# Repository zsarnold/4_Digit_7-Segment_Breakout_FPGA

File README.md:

# 4 Digit, 7-Segment Breakout FPGA

This breakout board was created to be used in my Ohio University Master's course. We were required to build this circuit on a breadboard but I wanted to help develop my PCB design skills. This is a 2 layer board and has 4 M3 mounting holes to add standoffs. This was designed using KiCAD and the PCB was produced by JLCPCB.

## Table of Contents
- [4 Digit, 7-Segment Breakout FPGA](#4-digit-7-segment-breakout-fpga)
  - [Table of Contents](#table-of-contents)
  - [BOM](#bom)
  - [Usage](#usage)
  - [License](#license)

## BOM
| Qty           | Reference     | Value         |
| ------------- | ------------- | ------------- |
| 1 | U1 | 4 Digit, 7-Segment Display |
| 1 | J1 | 1x13 2.54mm Header |
| 8 | R1-R8| 330&#937; (0603)
| 4 | R9-R12| 10k&#937; (0603)
| 4 | Q1-Q4| PN2222A (TO-92)
## Usage
## License

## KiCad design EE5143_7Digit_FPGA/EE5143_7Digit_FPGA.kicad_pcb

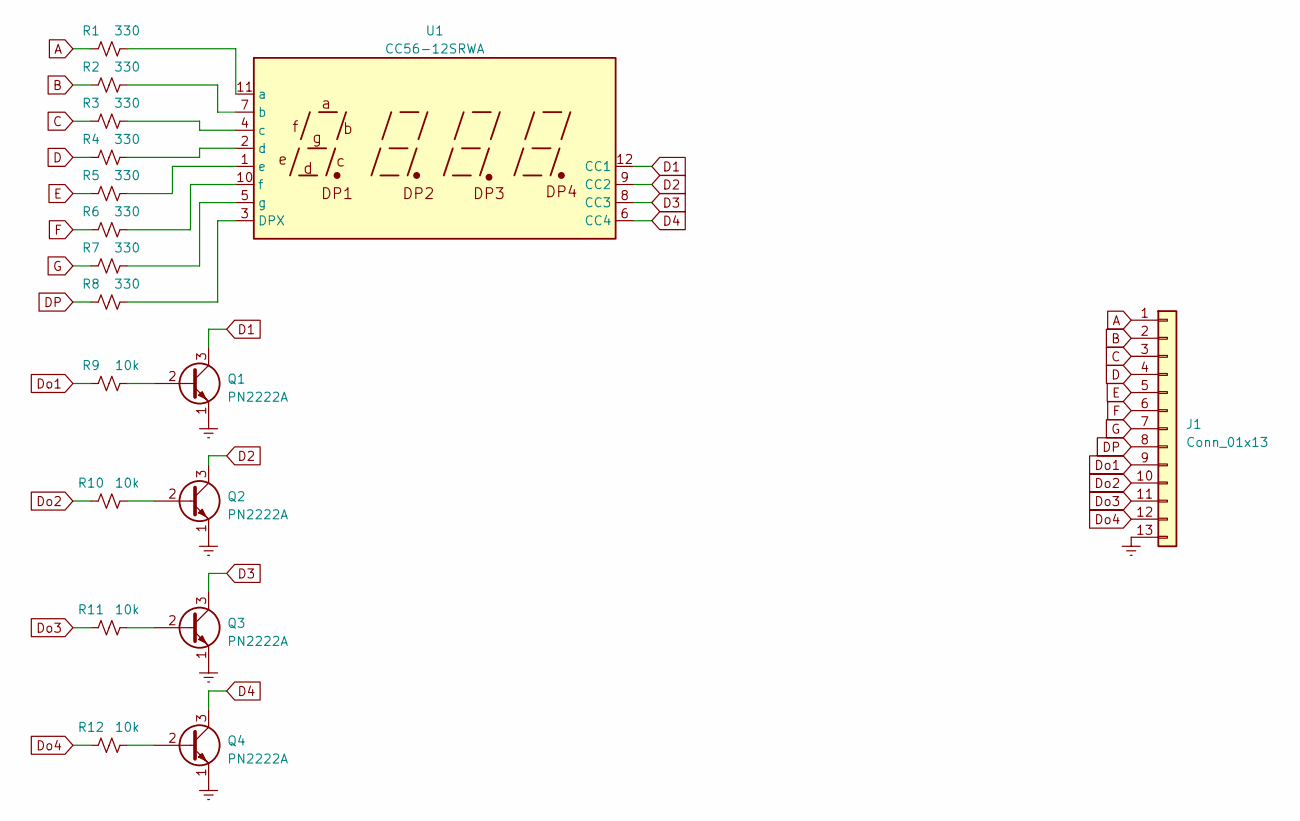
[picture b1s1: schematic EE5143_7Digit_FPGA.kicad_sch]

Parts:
J1: Conn_01x13; PinHeader_1x13_P2.54mm_Vertical
Q1, Q2, Q3, Q4: PN2222A; TO-92_Inline
R1, R2, R3, R4, R5, R6, R7, R8: 330; R_0603_1608Metric_Pad0.98x0.95mm_HandSolder
R9, R10, R11, R12: 10k; R_0603_1608Metric_Pad0.98x0.95mm_HandSolder
U1: CC56-12SRWA; CA56-12SRWA

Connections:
A: J1.1, R1.1
B: J1.2, R2.1
C: J1.3, R3.1
D: J1.4, R4.1
D1: Q1.3 (C), U1.12 (CC1)
D2: Q2.3 (C), U1.9 (CC2)
D3: Q3.3 (C), U1.8 (CC3)
D4: Q4.3 (C), U1.6 (CC4)
DP: J1.8, R8.1
Do1: J1.9, R9.1
Do2: J1.10, R10.1
Do3: J1.11, R11.1
Do4: J1.12, R12.1
E: J1.5, R5.1
F: J1.6, R6.1
G: J1.7, R7.1
GNDREF: J1.13, Q1.1 (E), Q2.1 (E), Q3.1 (E), Q4.1 (E)
unnamed: Q1.2 (B), R9.2
unnamed: Q2.2 (B), R10.2
unnamed: Q3.2 (B), R11.2
unnamed: Q4.2 (B), R12.2
unnamed: R8.2, U1.3 (DPX)
unnamed: R1.2, U1.11 (a)
unnamed: R2.2, U1.7 (b)
unnamed: R3.2, U1.4 (c)
unnamed: R4.2, U1.2 (d)
unnamed: R5.2, U1.1 (e)
unnamed: R6.2, U1.10 (f)
unnamed: R7.2, U1.5 (g)

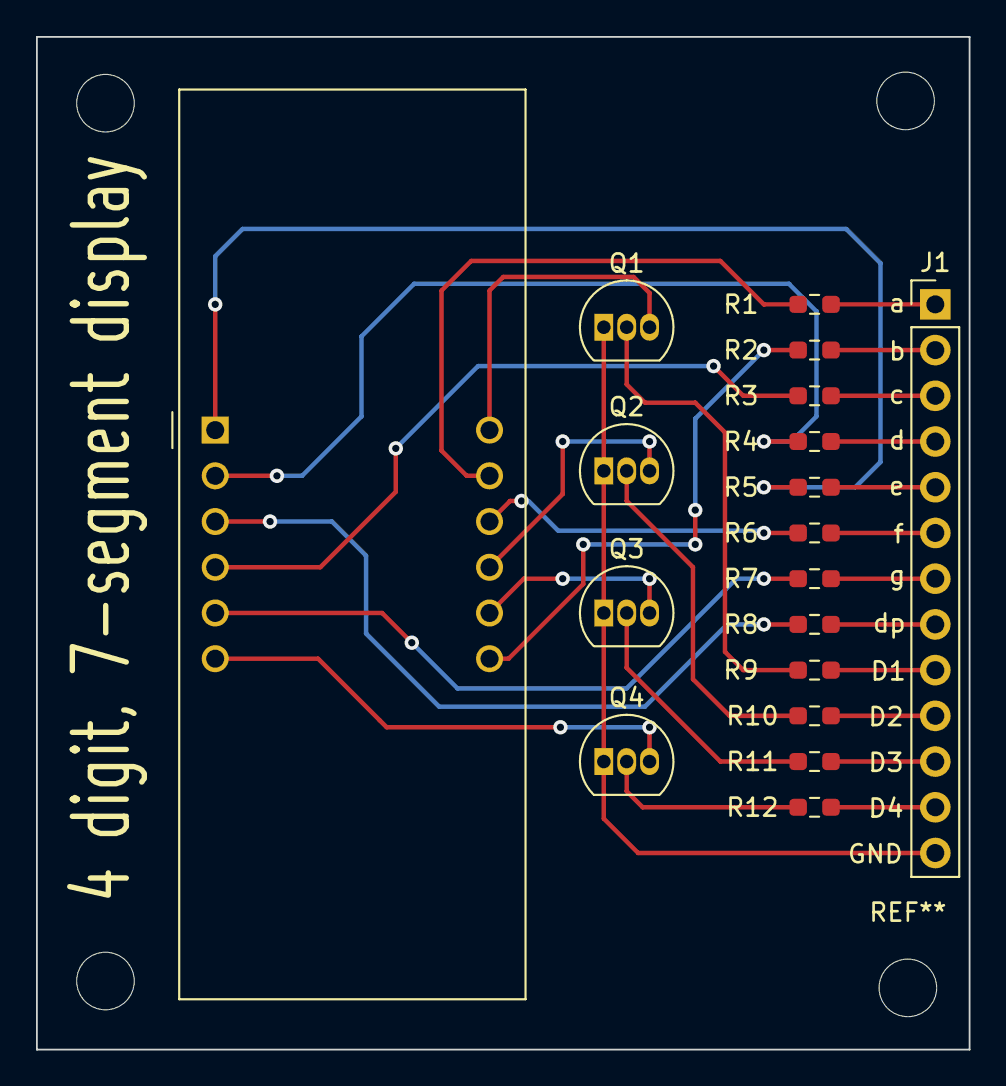
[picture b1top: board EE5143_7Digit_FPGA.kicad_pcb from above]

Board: 2 copper layers, 51.8 x 56.3 mm, 18 parts (0 on the bottom side), 29 nets.

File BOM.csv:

"Source:","/Users/zarnold/Documents/GitHub/7-Digit_FPGA/EE5143_7Digit_FPGA/EE5143_7Digit_FPGA.kicad_sch"
"Date:","Wednesday, May 08, 2024 at 10:34:42 PM"
"Tool:","Eeschema (7.0.0-0)"
"Generator:","/Applications/KiCad/KiCad.app/Contents/SharedSupport/plugins/bom_csv_grouped_by_value.py"
"Component Count:","18"

"Collated Components:"

"Item","Qty","Reference(s)","Value","LibPart","Footprint","Datasheet","DNP"
"1","1","J1","Conn_01x13","Connector_Generic:Conn_01x13","Connector_PinHeader_2.54mm:PinHeader_1x13_P2.54mm_Vertical","~","",""
"2","4","Q1, Q2, Q3, Q4","PN2222A","Transistor_BJT:PN2222A","Package_TO_SOT_THT:TO-92_Inline","https://www.onsemi.com/pub/Collateral/PN2222-D.PDF","",""
"3","8","R1, R2, R3, R4, R5, R6, R7, R8","330","Device:R_Small_US","Resistor_SMD:R_0603_1608Metric_Pad0.98x0.95mm_HandSolder","~","",""
"4","4","R9, R10, R11, R12","10k","Device:R_Small_US","Resistor_SMD:R_0603_1608Metric_Pad0.98x0.95mm_HandSolder","~","",""
"5","1","U1","CC56-12SRWA","Display_Character:CC56-12SRWA","Display_7Segment:CA56-12SRWA","http://www.kingbrightusa.com/images/catalog/SPEC/CC56-12SRWA.pdf","",""

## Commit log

2024-05-09 PCB commit
    This is the KiCAD files for the PCB
2024-05-09 Gerber outputs of the PCB
2024-05-09 Added files and updated title block of schematic
2024-05-09 Create LICENSE
